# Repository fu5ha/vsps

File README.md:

# VSPS

This is a design for a power supply board and casing for the [VSPS (Very Simple Phono Stage)](http://phonoclone.com/diy-pho5.html) from RJM Audio.

Includes PCB design for power supply board, ready-to-print and CAD files for casing and adapter plates for both power supply unit
and main unit.

## Main Unit

### Main unit BOM

You'll want a VSPS kit (or source your own) from RJM Audio: <http://phonoclone.com/pcb.html>

Connectors/receptacles BOM for the enclosure unit as designed: <https://www.mouser.com/ProjectManager/ProjectDetail.aspx?AccessID=c72ca91d05>

Then you'll want an enclosure. The CAD files have been designed for [this case](http://phonoclone.com/pcb.html) (the same one as for the power unit).

### CAD

Download zipped CAD files from [the Releases page](https://github.com/termhn/vsps-power/releases)

## Power Supply Unit

### Power supply BOM

Electronic parts BOM: <https://www.mouser.com/ProjectManager/ProjectDetail.aspx?AccessID=cfbaef526f>

Also, you'll need an enclosure. It is designed to work in this enclosure: <https://www.amazon.com/gp/product/B07HBT2CGK>

You'll need to sand down the sides of the PCB slightly at which point it will be a nice pressure fit into the PCB groove built into that enclosure.

### CAD

Download zipped CAD files from [the Releases page](https://github.com/termhn/vsps-power/releases)

### Gerbers

Download zipped gerbers from [the Releases page](https://github.com/termhn/vsps-power/releases)

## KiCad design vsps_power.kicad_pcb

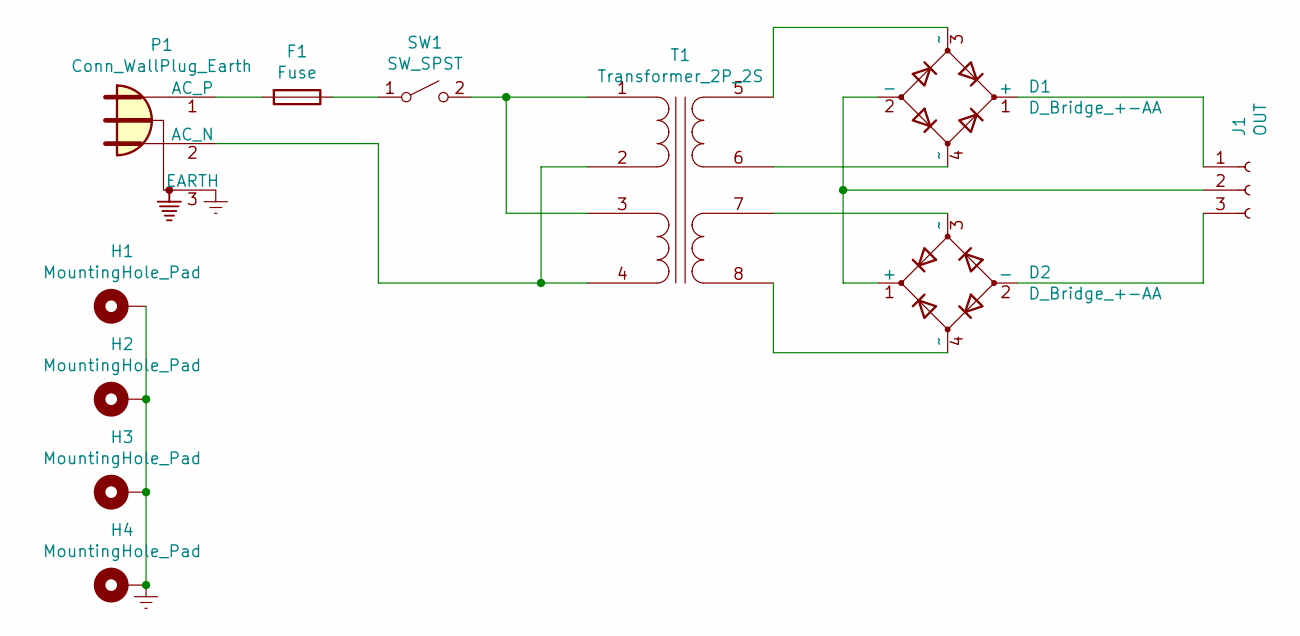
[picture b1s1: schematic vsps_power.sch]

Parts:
D1, D2: D_Bridge_+-AA; Diode_Bridge_15.1x15.1x6.3mm_P10.9mm
F1: Fuse; Fuseholder_5x20mm_DualClip
H1, H2, H3, H4: MountingHole_Pad; MountingHole_3.2mm_M3_Pad
J1: OUT; SolderWire-0.5sqmm_1x03_P4.6mm_D0.9mm_OD2.1mm
P1: Conn_WallPlug_Earth; SolderWire-1.5sqmm_1x03_P6mm_D1.7mm_OD3mm
SW1: SW_SPST; SolderWire-1.5sqmm_1x02_P6mm_D1.7mm_OD3mm
T1: Transformer_2P_2S; Transformer_Triad_FP24-250

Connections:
Earth: H1.1, H2.1, H3.1, H4.1, P1.3 (EARTH)
unnamed: D1.1 (+), J1.1
unnamed: D1.2 (-), D2.1 (+), J1.2
unnamed: D1.3 (~~), T1.5 (SA)
unnamed: D1.4 (~~), T1.6 (SB)
unnamed: D2.2 (-), J1.3
unnamed: D2.3 (~~), T1.7 (SC)
unnamed: D2.4 (~~), T1.8 (SD)
unnamed: F1.1, SW1.1 (A)
unnamed: F1.2, P1.1 (AC_P)
unnamed: P1.2 (AC_N), T1.2 (SB), T1.4 (SD)
unnamed: SW1.2 (B), T1.1 (SA), T1.3 (SC)

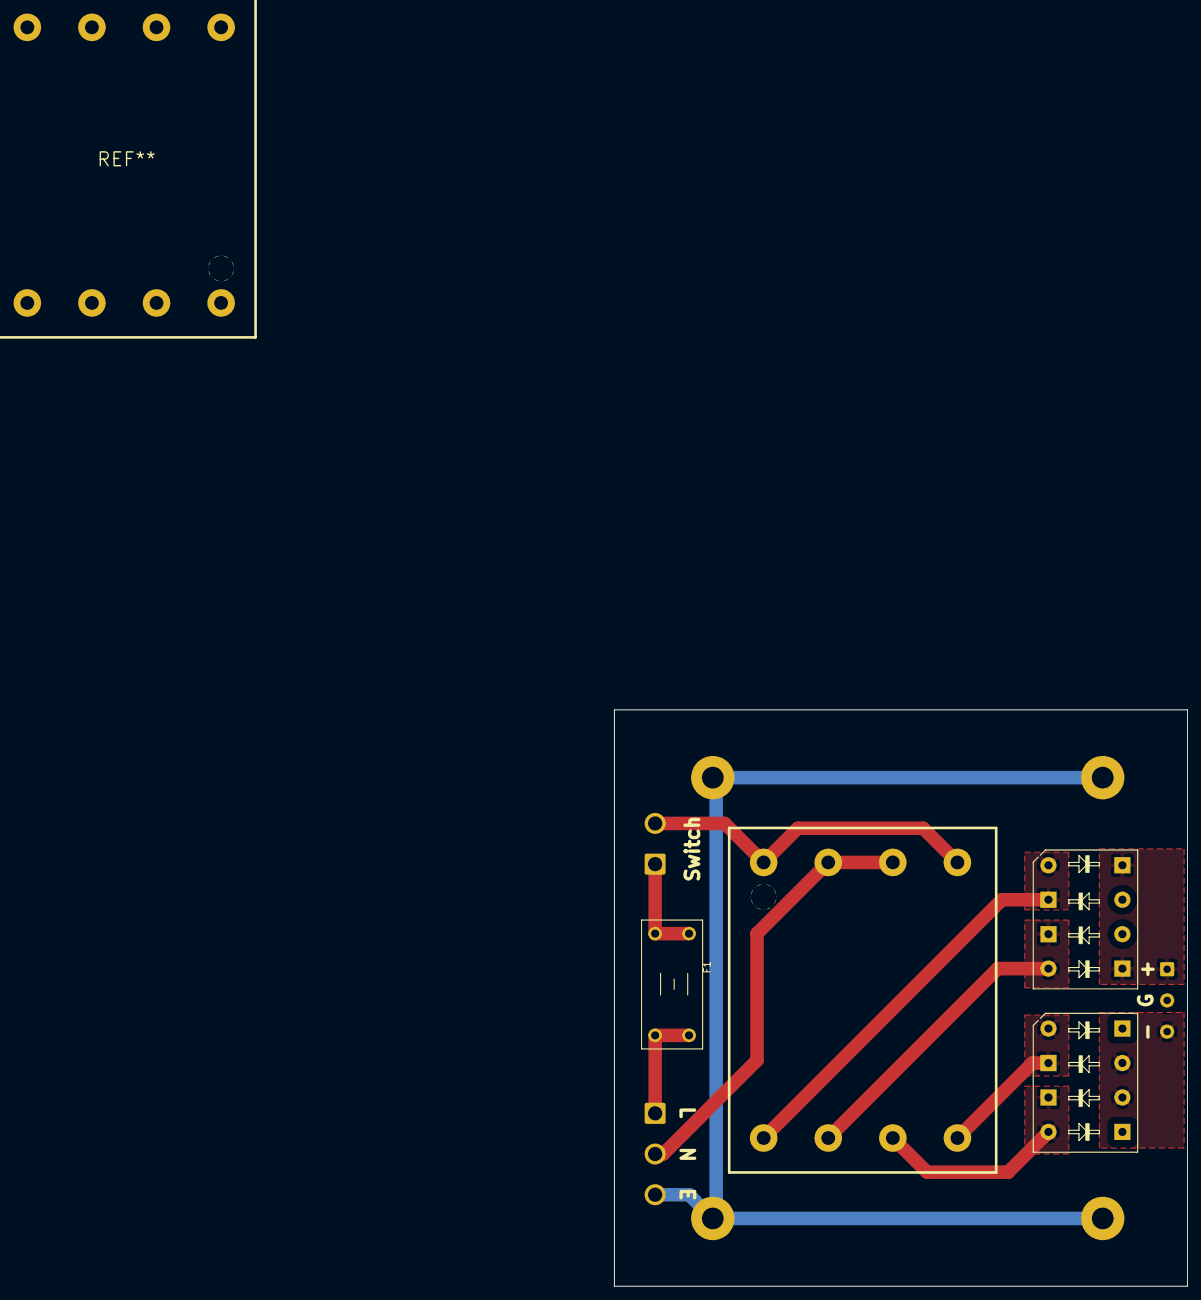
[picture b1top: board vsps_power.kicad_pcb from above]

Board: 2 copper layers, 84.5 x 85.0 mm, 11 parts (1 on the bottom side), 12 nets.

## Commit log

2021-04-03 add releases link to readme
2021-04-03 add front plate stl
2021-04-03 add license
2021-04-05 add cad and section about main unit
2021-04-05 correct transformer footprint
